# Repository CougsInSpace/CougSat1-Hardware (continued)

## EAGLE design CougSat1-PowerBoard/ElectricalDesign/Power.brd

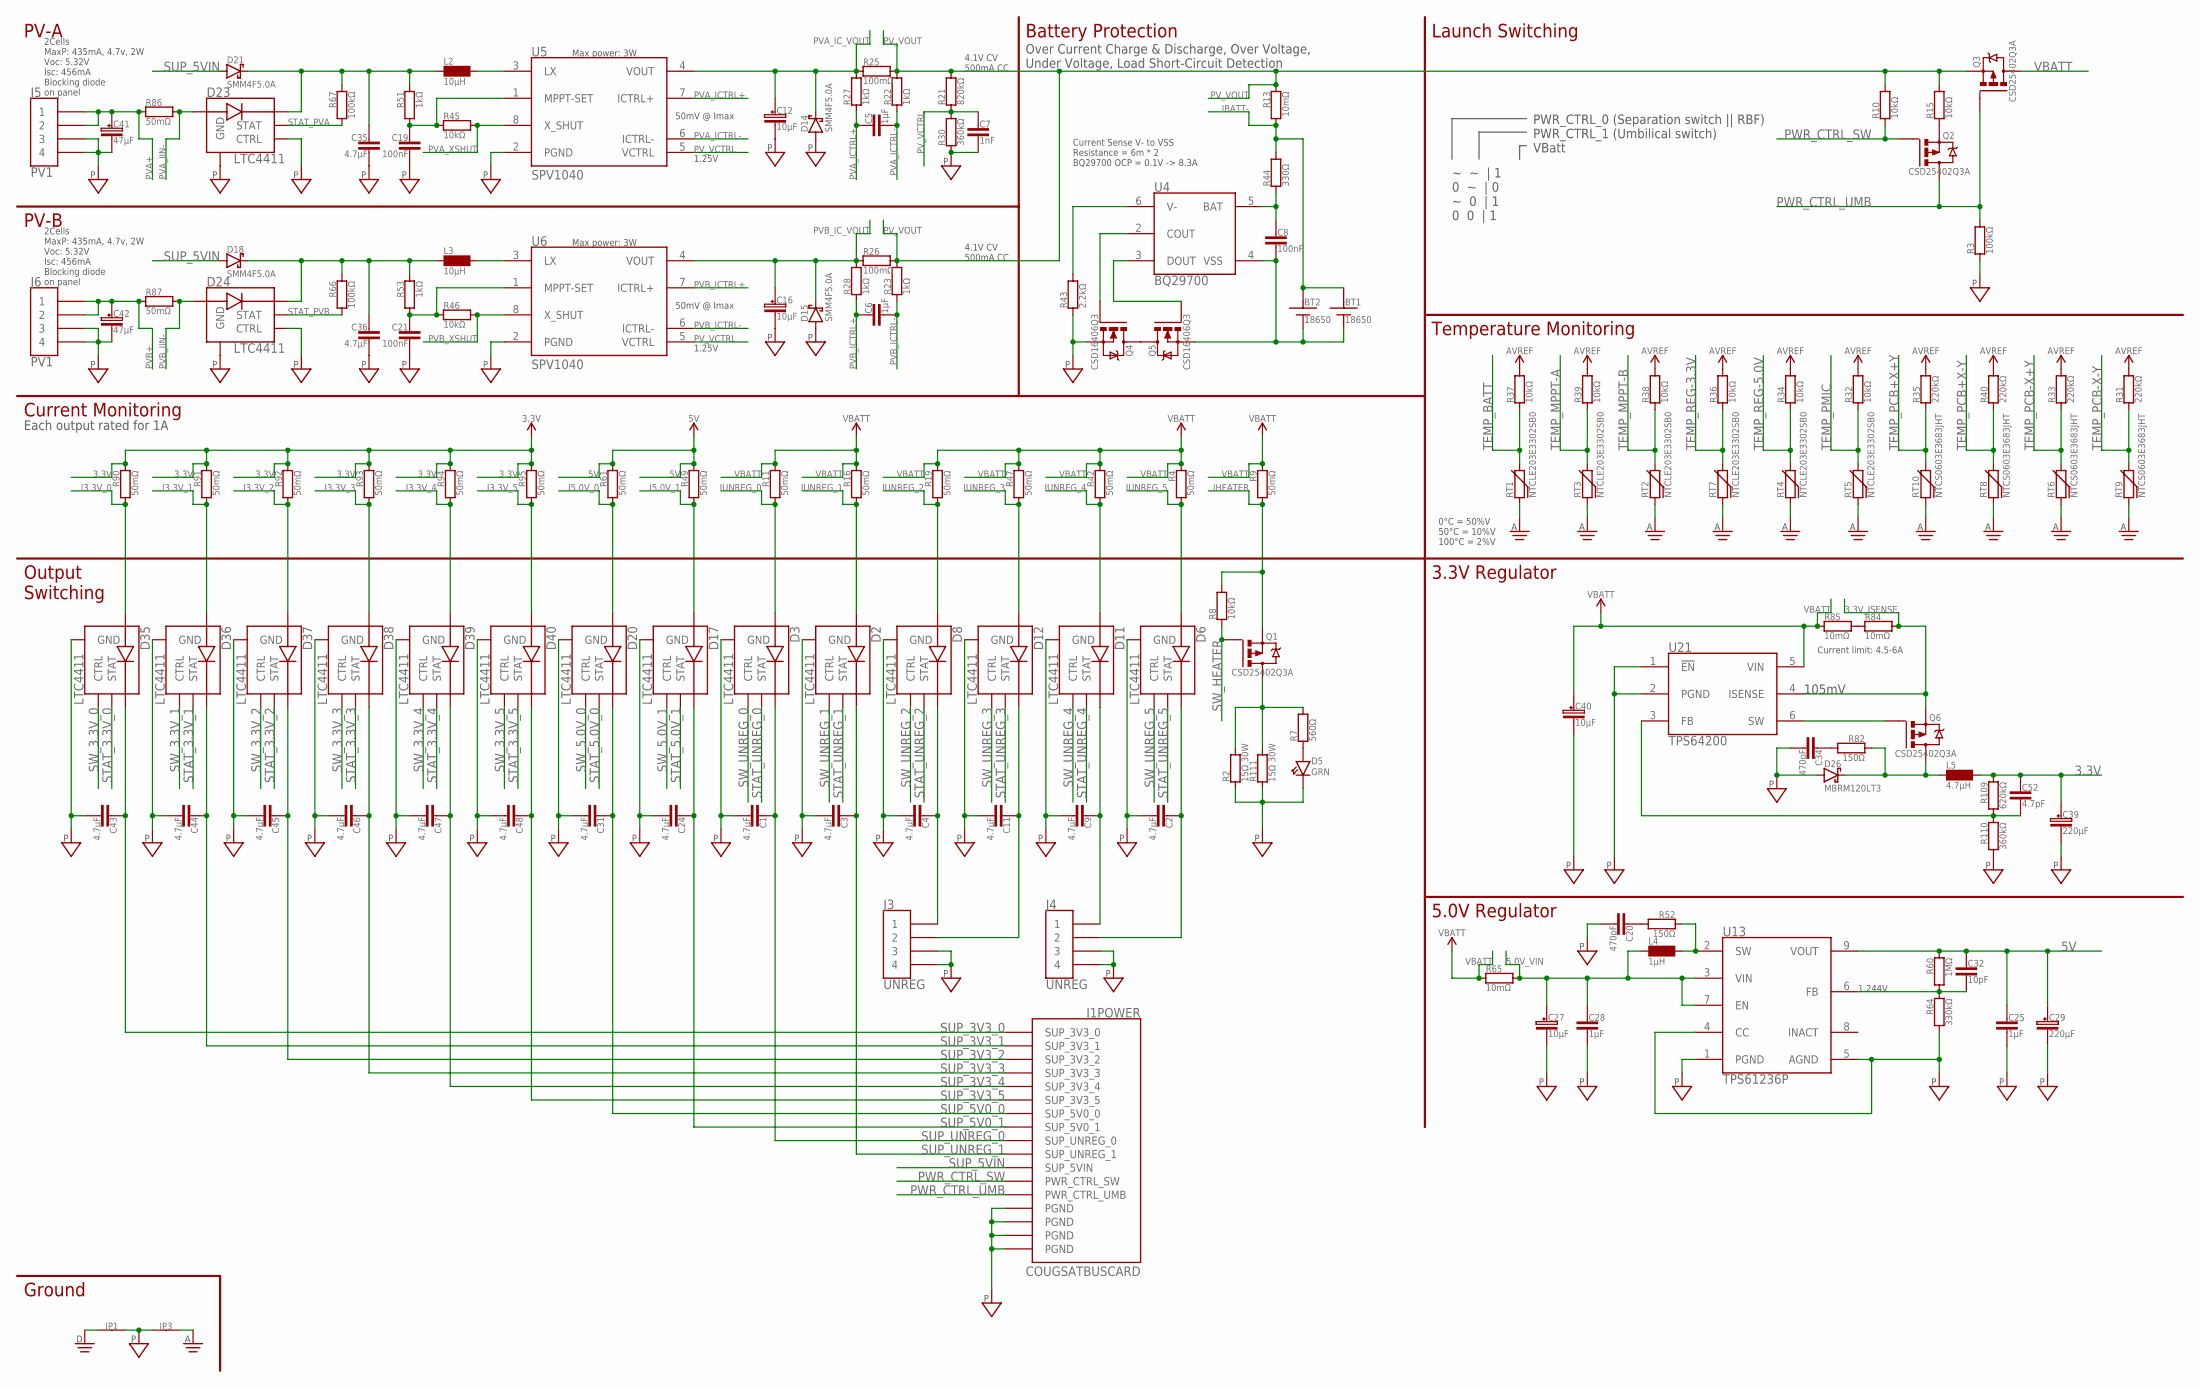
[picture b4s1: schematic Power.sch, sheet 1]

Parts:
BT1, BT2: 18650; BAT-18650SOLDER
C1, C2, C3, C4, C9, C11, C24, C31, C35, C36, C43, C44, C45, C46, C47, C48: 4.7µF; 3216
C5, C6, C25, C28: 1µF; 1608
C7: 1nF; 1608
C8, C19, C21: 100nF; 1608
C12, C16, C27, C40: 10µF; 4028-POL
C20, C34: 470pF; 1608
C29, C39: 220µF; 7132-POL
C32: 10pF; 1608
C41, C42: 47µF; 4028-POL
C52: 4.7pF; 1608
D2, D3, D6, D8, D11, D12, D17, D20, D23, D24, D35, D36, D37, D38, D39, D40: LTC4411; SOT23-5
D5: GRN; 1608-POL
D14, D15, D18, D21: SMM4F5.0A; STMITE
D26: MBRM120LT3; POWERMITE1
J1: COUGSATBUSCARD; COUGSATBUS_MALE-SODIMM
J3, J4: UNREG; 1X04_PICOLOCK1.5MM
J5, J6: PV1; 1X04_PICOLOCK1.5MM
JP1, JP3: SHORTCIRCUIT1608JUMPER; 1608
L2, L3: 10µH; INDUCTOR-LPS6235
L4: 1µH; INDUCTOR-XAL7030
L5: 4.7µH; INDUCTOR-XAL7030
Q1, Q2, Q3, Q6: CSD25402Q3A; SON-3.3X3.3MM
Q4, Q5: CSD16406Q3; SON-3.3X3.3MM
R2, R111: 15Ω 30W; TO220-2
R3, R66, R67: 100kΩ; 1608
R4, R9, R11, R16, R19, R42, R47, R49, R61, R86, R87, R90, R91, R92, R93, R94, R95: 50mΩ; 1608
R7: 560Ω; 1608
R8, R10, R15, R32, R34, R36, R37, R38, R39, R45, R46: 10kΩ; 1608
R13, R65, R84, R85: 10mΩ; 3216
R21: 820kΩ; 1608
R22, R23, R27, R28, R51, R53: 1kΩ; 1608
R25, R26: 100mΩ; 1608
R30, R110: 360kΩ; 1608
R31, R33, R35, R40: 220kΩ; 1608
R43: 2.2kΩ; 1608
R44: 330Ω; 1608
R52, R82: 150Ω; 1608
R60: 1MΩ; 1608
R64: 330kΩ; 1608
R109: 620kΩ; 1608
RT1, RT2, RT3, RT4, RT5, RT7: NTCLE203E3302SB0; 1X02_THERMISTOR
RT6, RT8, RT9, RT10: NTCS0603E3683JHT; 1608
U4: BQ29700; SON6-1.5X1.5MM
U5, U6: SPV1040; TSSOP8
U13: TPS61236P; QFN-TPS61236P
U21: TPS64200; SOT23-6

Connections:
3.3V: C39.A, C52.1, L5.2 (1), R90.1, R91.1, R92.1, R93.1, R94.1, R95.1, R109.1; also elsewhere on the board
3.3V_FB: C52.2, R109.2, R110.1, U21.3 (FB)
3.3V_ISENSE: Q6.5 (S), Q6.6 (S), Q6.7 (S), Q6.8 (S), Q6.PAD (S), R84.2, U21.4 (ISENSE); also elsewhere on the board
3.3V_LSW: D26.C, L5.11 (2), Q6.1 (D), Q6.2 (D), Q6.3 (D), R82.1
3.3V_RISENSE: R84.1, R85.2
3.3V_SNUBBER: C34.1, R82.2
3.3V_SW: Q6.4 (G), U21.6 (SW)
5.0V_FB: C32.2, R60.2, R64.1, U13.6 (FB)
5.0V_SNUBBER: C20.1, R52.2
5.0V_SW: L4.2 (1), R52.1, U13.2 (SW)
5.0V_VIN: C27.A, C28.1, L4.11 (2), R65.2, U13.3 (VIN), U13.7 (EN); also elsewhere on the board
5V: C25.1, C29.A, C32.1, R49.1, R60.1, R61.1, U13.9 (VOUT); also elsewhere on the board
AGND: JP3.2, RT1.1, RT2.1, RT3.1, RT4.1, RT5.1, RT6.1, RT7.1, RT8.1, RT9.1, RT10.1; also elsewhere on the board
AVREF: R31.2, R32.2, R33.2, R34.2, R35.2, R36.2, R37.2, R38.2, R39.2, R40.2; also elsewhere on the board
BATTPROTECTDOUT: Q5.4 (G), U4.3 (DOUT)
BATTPROTECT_BAT: C8.1, R44.1, U4.5 (BAT)
BATTPROTECT_COUT: Q4.4 (G), U4.2 (COUT)
BATTPROTECT_SW: Q4.5 (D), Q4.6 (D), Q4.7 (D), Q4.8 (D), Q4.PAD (D), Q5.5 (D), Q5.6 (D), Q5.7 (D), Q5.8 (D), Q5.PAD (D)
BATTPROTECT_V-: R43.2, U4.6 (V-)
BATTPROTECT_VSS: BT1.A, BT2.A, C8.2, Q5.1 (S), Q5.2 (S), Q5.3 (S), U4.4 (VSS)
DGND: JP1.1; also elsewhere on the board
I3.3V_0: D35.1 (IN), R90.2; also elsewhere on the board
I3.3V_1: D36.1 (IN), R91.2; also elsewhere on the board
I3.3V_2: D37.1 (IN), R92.2; also elsewhere on the board
I3.3V_3: D38.1 (IN), R93.2; also elsewhere on the board
I3.3V_4: D39.1 (IN), R94.2; also elsewhere on the board
I3.3V_5: D40.1 (IN), R95.2; also elsewhere on the board
I5.0V_0: D20.1 (IN), R61.2; also elsewhere on the board
I5.0V_1: D17.1 (IN), R49.2; also elsewhere on the board
IBATT-: BT1.C, BT2.C, R13.2, R44.2; also elsewhere on the board
IHEATER: Q1.5 (S), Q1.6 (S), Q1.7 (S), Q1.8 (S), Q1.PAD (S), R8.2, R9.2; also elsewhere on the board
IUNREG_0: D3.1 (IN), R11.2; also elsewhere on the board
IUNREG_1: D2.1 (IN), R16.2; also elsewhere on the board
IUNREG_2: D8.1 (IN), R19.2; also elsewhere on the board
IUNREG_3: D12.1 (IN), R47.2; also elsewhere on the board
IUNREG_4: D11.1 (IN), R42.2; also elsewhere on the board
IUNREG_5: D6.1 (IN), R4.2; also elsewhere on the board
MPPTA_VIN: C35.1, D21.A (C), D23.5 (OUT), L2.2, R51.1, R67.1
MPPTB_VIN: C36.1, D18.A (C), D24.5 (OUT), L3.2, R53.1, R66.1
PGND: C1.2, C2.2, C3.2, C4.2, C7.2, C9.2, C11.2, C12.C, C16.C, C19.2, C20.2, C21.2, C24.2, C25.2, C27.C, C28.2, C29.C, C31.2, C34.2, C35.2, C36.2, C39.C, C40.C, C41.C, C42.C, C43.2, C44.2, C45.2, C46.2, C47.2, C48.2, D2.2 (GND), D3.2 (GND), D5.C, D6.2 (GND), D8.2 (GND), D11.2 (GND), D12.2 (GND), D14.C (A), D15.C (A), D17.2 (GND), D20.2 (GND), D23.2 (GND), D23.3 (CTRL), D24.2 (GND), D24.3 (CTRL), D26.A, D35.2 (GND), D36.2 (GND), D37.2 (GND), D38.2 (GND), D39.2 (GND), D40.2 (GND), J1.1 (PGND), J1.3 (PGND), J1.5 (PGND), J1.7 (PGND), J1.9 (PGND), J1.11 (PGND), J1.13 (PGND), J1.15 (PGND), J1.17 (PGND), J1.19 (PGND), J1.41 (PGND), J1.43 (PGND), J1.45 (PGND), J1.47 (PGND), J1.49 (PGND), J1.51 (PGND), J1.53 (PGND), J1.55 (PGND), J1.57 (PGND), J1.59 (PGND), J1.61 (PGND), J1.63 (PGND), J1.65 (PGND), J1.67 (PGND), J1.69 (PGND), J1.82 (PGND), J1.84 (PGND), J1.86 (PGND), J1.88 (PGND), J1.90 (PGND), J1.92 (PGND), J1.94 (PGND), J1.96 (PGND), J1.98 (PGND), J1.100 (PGND), J1.102 (PGND), J1.104 (PGND), J1.106 (PGND), J1.108 (PGND), J1.110 (PGND), J1.112 (PGND), J1.114 (PGND), J1.116 (PGND), J1.118 (PGND), J1.120 (PGND), J1.122 (PGND), J1.124 (PGND), J1.126 (PGND), J1.128 (PGND), J1.130 (PGND), J1.131 (PGND), J1.132 (PGND), J1.133 (PGND), J1.134 (PGND), J1.135 (PGND), J1.136 (PGND), J1.137 (PGND), J1.138 (PGND), J1.139 (PGND), J1.140 (PGND), J3.3, J3.4, J4.3, J4.4, J5.3, J5.4, J6.3, J6.4, JP1.2, JP3.1, Q4.1 (S), Q4.2 (S), Q4.3 (S), R2.1, R3.1, R30.1, R43.1, R64.2, R110.2, R111.1, U5.2 (PGND), U6.2 (PGND), U13.1 (PGND), U13.4 (CC), U13.5 (AGND), U21.1 (!EN), U21.2 (PGND); also elsewhere on the board
PVA+: C41.A, J5.1, J5.2, R86.1; also elsewhere on the board
PVA_ICTRL+: C5.1, R27.1, U5.7 (ICTRL+)
PVA_ICTRL-: C5.2, R22.1, U5.6 (ICTRL-)
PVA_IC_VOUT: C12.A, D14.A (C), R25.1, R27.2, U5.4 (VOUT); also elsewhere on the board
PVA_IIN-: D23.1 (IN), R86.2; also elsewhere on the board
PVA_LX: L2.1, U5.3 (LX)
PVA_MPPTSET: C19.1, R45.1, R51.2, U5.1 (MPPT-SET)
PVA_XSHUT: R45.2, U5.8 (X_SHUT); also elsewhere on the board
PVB+: C42.A, J6.1, J6.2, R87.1; also elsewhere on the board
PVB_ICTRL+: C6.1, R28.1, U6.7 (ICTRL+)
PVB_ICTRL-: C6.2, R23.1, U6.6 (ICTRL-)
PVB_IC_VOUT: C16.A, D15.A (C), R26.1, R28.2, U6.4 (VOUT); also elsewhere on the board
PVB_IIN-: D24.1 (IN), R87.2; also elsewhere on the board
PVB_LX: L3.1, U6.3 (LX)
PVB_MPPTSET: C21.1, R46.1, R53.2, U6.1 (MPPT-SET)
PVB_XSHUT: R46.2, U6.8 (X_SHUT); also elsewhere on the board
PV_VCTRL: C7.1, R21.1, R30.2, U5.5 (VCTRL), U6.5 (VCTRL)
PV_VOUT: Q3.5 (S), Q3.6 (S), Q3.7 (S), Q3.8 (S), Q3.PAD (S), R10.2, R13.1, R15.2, R21.2, R22.2, R23.2, R25.2, R26.2; also elsewhere on the board
PWR_CTRL_0_SW+: Q2.5 (S), Q2.6 (S), Q2.7 (S), Q2.8 (S), Q2.PAD (S), R15.1
PWR_CTRL_SW: J1.166 (PWR_CTRL_SW), J1.168 (PWR_CTRL_SW), Q2.4 (G), R10.1
PWR_CTRL_UMB: J1.170 (PWR_CTRL_UMB), J1.172 (PWR_CTRL_UMB), Q2.1 (D), Q2.2 (D), Q2.3 (D), Q3.4 (G), R3.2
STAT_3.3V_0: D35.4 (STAT); also elsewhere on the board
STAT_3.3V_1: D36.4 (STAT); also elsewhere on the board
STAT_3.3V_2: D37.4 (STAT); also elsewhere on the board
STAT_3.3V_3: D38.4 (STAT); also elsewhere on the board
STAT_3.3V_4: D39.4 (STAT); also elsewhere on the board
STAT_3.3V_5: D40.4 (STAT); also elsewhere on the board
STAT_5.0V_0: D20.4 (STAT); also elsewhere on the board
STAT_5.0V_1: D17.4 (STAT); also elsewhere on the board
STAT_HEATER: D5.A, R7.1
STAT_PVA: D23.4 (STAT), R67.2; also elsewhere on the board
STAT_PVB: D24.4 (STAT), R66.2; also elsewhere on the board
STAT_UNREG_0: D3.4 (STAT); also elsewhere on the board
STAT_UNREG_1: D2.4 (STAT); also elsewhere on the board
STAT_UNREG_2: D8.4 (STAT); also elsewhere on the board
STAT_UNREG_3: D12.4 (STAT); also elsewhere on the board
STAT_UNREG_4: D11.4 (STAT); also elsewhere on the board
STAT_UNREG_5: D6.4 (STAT); also elsewhere on the board
SUP_3V3_0: C43.1, D35.5 (OUT), J1.2 (SUP_3V3_0), J1.4 (SUP_3V3_0), J1.6 (SUP_3V3_0), J1.8 (SUP_3V3_0), J1.10 (SUP_3V3_0)
SUP_3V3_1: C44.1, D36.5 (OUT), J1.12 (SUP_3V3_1), J1.14 (SUP_3V3_1), J1.16 (SUP_3V3_1), J1.18 (SUP_3V3_1), J1.20 (SUP_3V3_1)
SUP_3V3_2: C45.1, D37.5 (OUT), J1.21 (SUP_3V3_2), J1.23 (SUP_3V3_2), J1.25 (SUP_3V3_2), J1.27 (SUP_3V3_2), J1.29 (SUP_3V3_2), J1.31 (SUP_3V3_2), J1.33 (SUP_3V3_2), J1.35 (SUP_3V3_2), J1.37 (SUP_3V3_2), J1.39 (SUP_3V3_2)
SUP_3V3_3: C46.1, D38.5 (OUT), J1.22 (SUP_3V3_3), J1.24 (SUP_3V3_3), J1.26 (SUP_3V3_3), J1.28 (SUP_3V3_3), J1.30 (SUP_3V3_3), J1.32 (SUP_3V3_3), J1.34 (SUP_3V3_3), J1.36 (SUP_3V3_3), J1.38 (SUP_3V3_3), J1.40 (SUP_3V3_3)
SUP_3V3_4: C47.1, D39.5 (OUT), J1.42 (SUP_3V3_4), J1.44 (SUP_3V3_4), J1.46 (SUP_3V3_4), J1.48 (SUP_3V3_4), J1.50 (SUP_3V3_4)
SUP_3V3_5: C48.1, D40.5 (OUT), J1.52 (SUP_3V3_5), J1.54 (SUP_3V3_5), J1.56 (SUP_3V3_5), J1.58 (SUP_3V3_5), J1.60 (SUP_3V3_5)
SUP_5V0_0: C31.1, D20.5 (OUT), J1.62 (SUP_5V0_0), J1.64 (SUP_5V0_0), J1.66 (SUP_5V0_0), J1.68 (SUP_5V0_0), J1.70 (SUP_5V0_0), J1.72 (SUP_5V0_0), J1.74 (SUP_5V0_0), J1.76 (SUP_5V0_0), J1.78 (SUP_5V0_0), J1.80 (SUP_5V0_0)
SUP_5V0_1: C24.1, D17.5 (OUT), J1.71 (SUP_5V0_1), J1.73 (SUP_5V0_1), J1.75 (SUP_5V0_1), J1.77 (SUP_5V0_1), J1.79 (SUP_5V0_1), J1.81 (SUP_5V0_1), J1.83 (SUP_5V0_1), J1.85 (SUP_5V0_1), J1.87 (SUP_5V0_1), J1.89 (SUP_5V0_1)
SUP_5VIN: D18.C (A), D21.C (A), J1.182 (SUP_5VIN), J1.184 (SUP_5VIN), J1.186 (SUP_5VIN), J1.188 (SUP_5VIN), J1.190 (SUP_5VIN), J1.192 (SUP_5VIN), J1.194 (SUP_5VIN), J1.196 (SUP_5VIN), J1.198 (SUP_5VIN), J1.200 (SUP_5VIN)
SUP_HEATER: Q1.1 (D), Q1.2 (D), Q1.3 (D), R2.3 (2), R7.2, R111.3 (2)
SUP_UNREG_0: C1.1, D3.5 (OUT), J1.91 (SUP_UNREG_0), J1.93 (SUP_UNREG_0), J1.95 (SUP_UNREG_0), J1.97 (SUP_UNREG_0), J1.99 (SUP_UNREG_0), J1.101 (SUP_UNREG_0), J1.103 (SUP_UNREG_0), J1.105 (SUP_UNREG_0), J1.107 (SUP_UNREG_0), J1.109 (SUP_UNREG_0)
SUP_UNREG_1: C3.1, D2.5 (OUT), J1.111 (SUP_UNREG_1), J1.113 (SUP_UNREG_1), J1.115 (SUP_UNREG_1), J1.117 (SUP_UNREG_1), J1.119 (SUP_UNREG_1), J1.121 (SUP_UNREG_1), J1.123 (SUP_UNREG_1), J1.125 (SUP_UNREG_1), J1.127 (SUP_UNREG_1), J1.129 (SUP_UNREG_1)
SUP_UNREG_2: C4.1, D8.5 (OUT), J3.1
SUP_UNREG_3: C11.1, D12.5 (OUT), J3.2
SUP_UNREG_4: C9.1, D11.5 (OUT), J4.1
SUP_UNREG_5: C2.1, D6.5 (OUT), J4.2
SW_3.3V_0: D35.3 (CTRL); also elsewhere on the board
SW_3.3V_1: D36.3 (CTRL); also elsewhere on the board
SW_3.3V_2: D37.3 (CTRL); also elsewhere on the board
SW_3.3V_3: D38.3 (CTRL); also elsewhere on the board
SW_3.3V_4: D39.3 (CTRL); also elsewhere on the board
SW_3.3V_5: D40.3 (CTRL); also elsewhere on the board
SW_5.0V_0: D20.3 (CTRL); also elsewhere on the board
SW_5.0V_1: D17.3 (CTRL); also elsewhere on the board
SW_HEATER: Q1.4 (G), R8.1; also elsewhere on the board
SW_UNREG_0: D3.3 (CTRL); also elsewhere on the board
SW_UNREG_1: D2.3 (CTRL); also elsewhere on the board
SW_UNREG_2: D8.3 (CTRL); also elsewhere on the board
SW_UNREG_3: D12.3 (CTRL); also elsewhere on the board
SW_UNREG_4: D11.3 (CTRL); also elsewhere on the board
SW_UNREG_5: D6.3 (CTRL); also elsewhere on the board
TEMP_BATT: R37.1, RT1.2; also elsewhere on the board
TEMP_MPPT-A: R39.1, RT3.2; also elsewhere on the board
TEMP_MPPT-B: R38.1, RT2.2; also elsewhere on the board
TEMP_PCB+X+Y: R35.1, RT10.2; also elsewhere on the board
TEMP_PCB+X-Y: R40.1, RT8.2; also elsewhere on the board
TEMP_PCB-X+Y: R33.1, RT6.2; also elsewhere on the board
TEMP_PCB-X-Y: R31.1, RT9.2; also elsewhere on the board
TEMP_PMIC: R32.1, RT5.2; also elsewhere on the board
TEMP_REG-3.3V: R36.1, RT7.2; also elsewhere on the board
TEMP_REG-5.0V: R34.1, RT4.2; also elsewhere on the board
VBATT: C40.A, Q3.1 (D), Q3.2 (D), Q3.3 (D), R4.1, R9.1, R11.1, R16.1, R19.1, R42.1, R47.1, R65.1, R85.1, U21.5 (VIN); also elsewhere on the board

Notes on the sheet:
2Cells MaxP: 435mA, 4.7v, 2W Voc: 5.32V Isc: 456mA Blocking diode on panel
PV-A
Max power: 3W
50mV @ Imax
1.25V
PV-B
Current Monitoring
Ground
Each output rated for 1A
4.1V CV 500mA CC
Battery Protection
Current Sense V- to VSS Resistance = 6m * 2 BQ29700 OCP = 0.1V -> 8.3A
Over Current Charge & Discharge, Over Voltage, Under Voltage, Load Short-Circuit Detection
Launch Switching
~ ~ | 1 0 ~ | 0 ~ 0 | 1 0 0 | 1
PWR_CTRL_0 (Separation switch || RBF) PWR_CTRL_1 (Umbilical switch) VBatt
Output Switching
3.3V Regulator
5.0V Regulator
105mV
Current limit: 4.5-6A
1.244V
Temperature Monitoring
0°C = 50%V 50°C = 10%V 100°C = 2%V

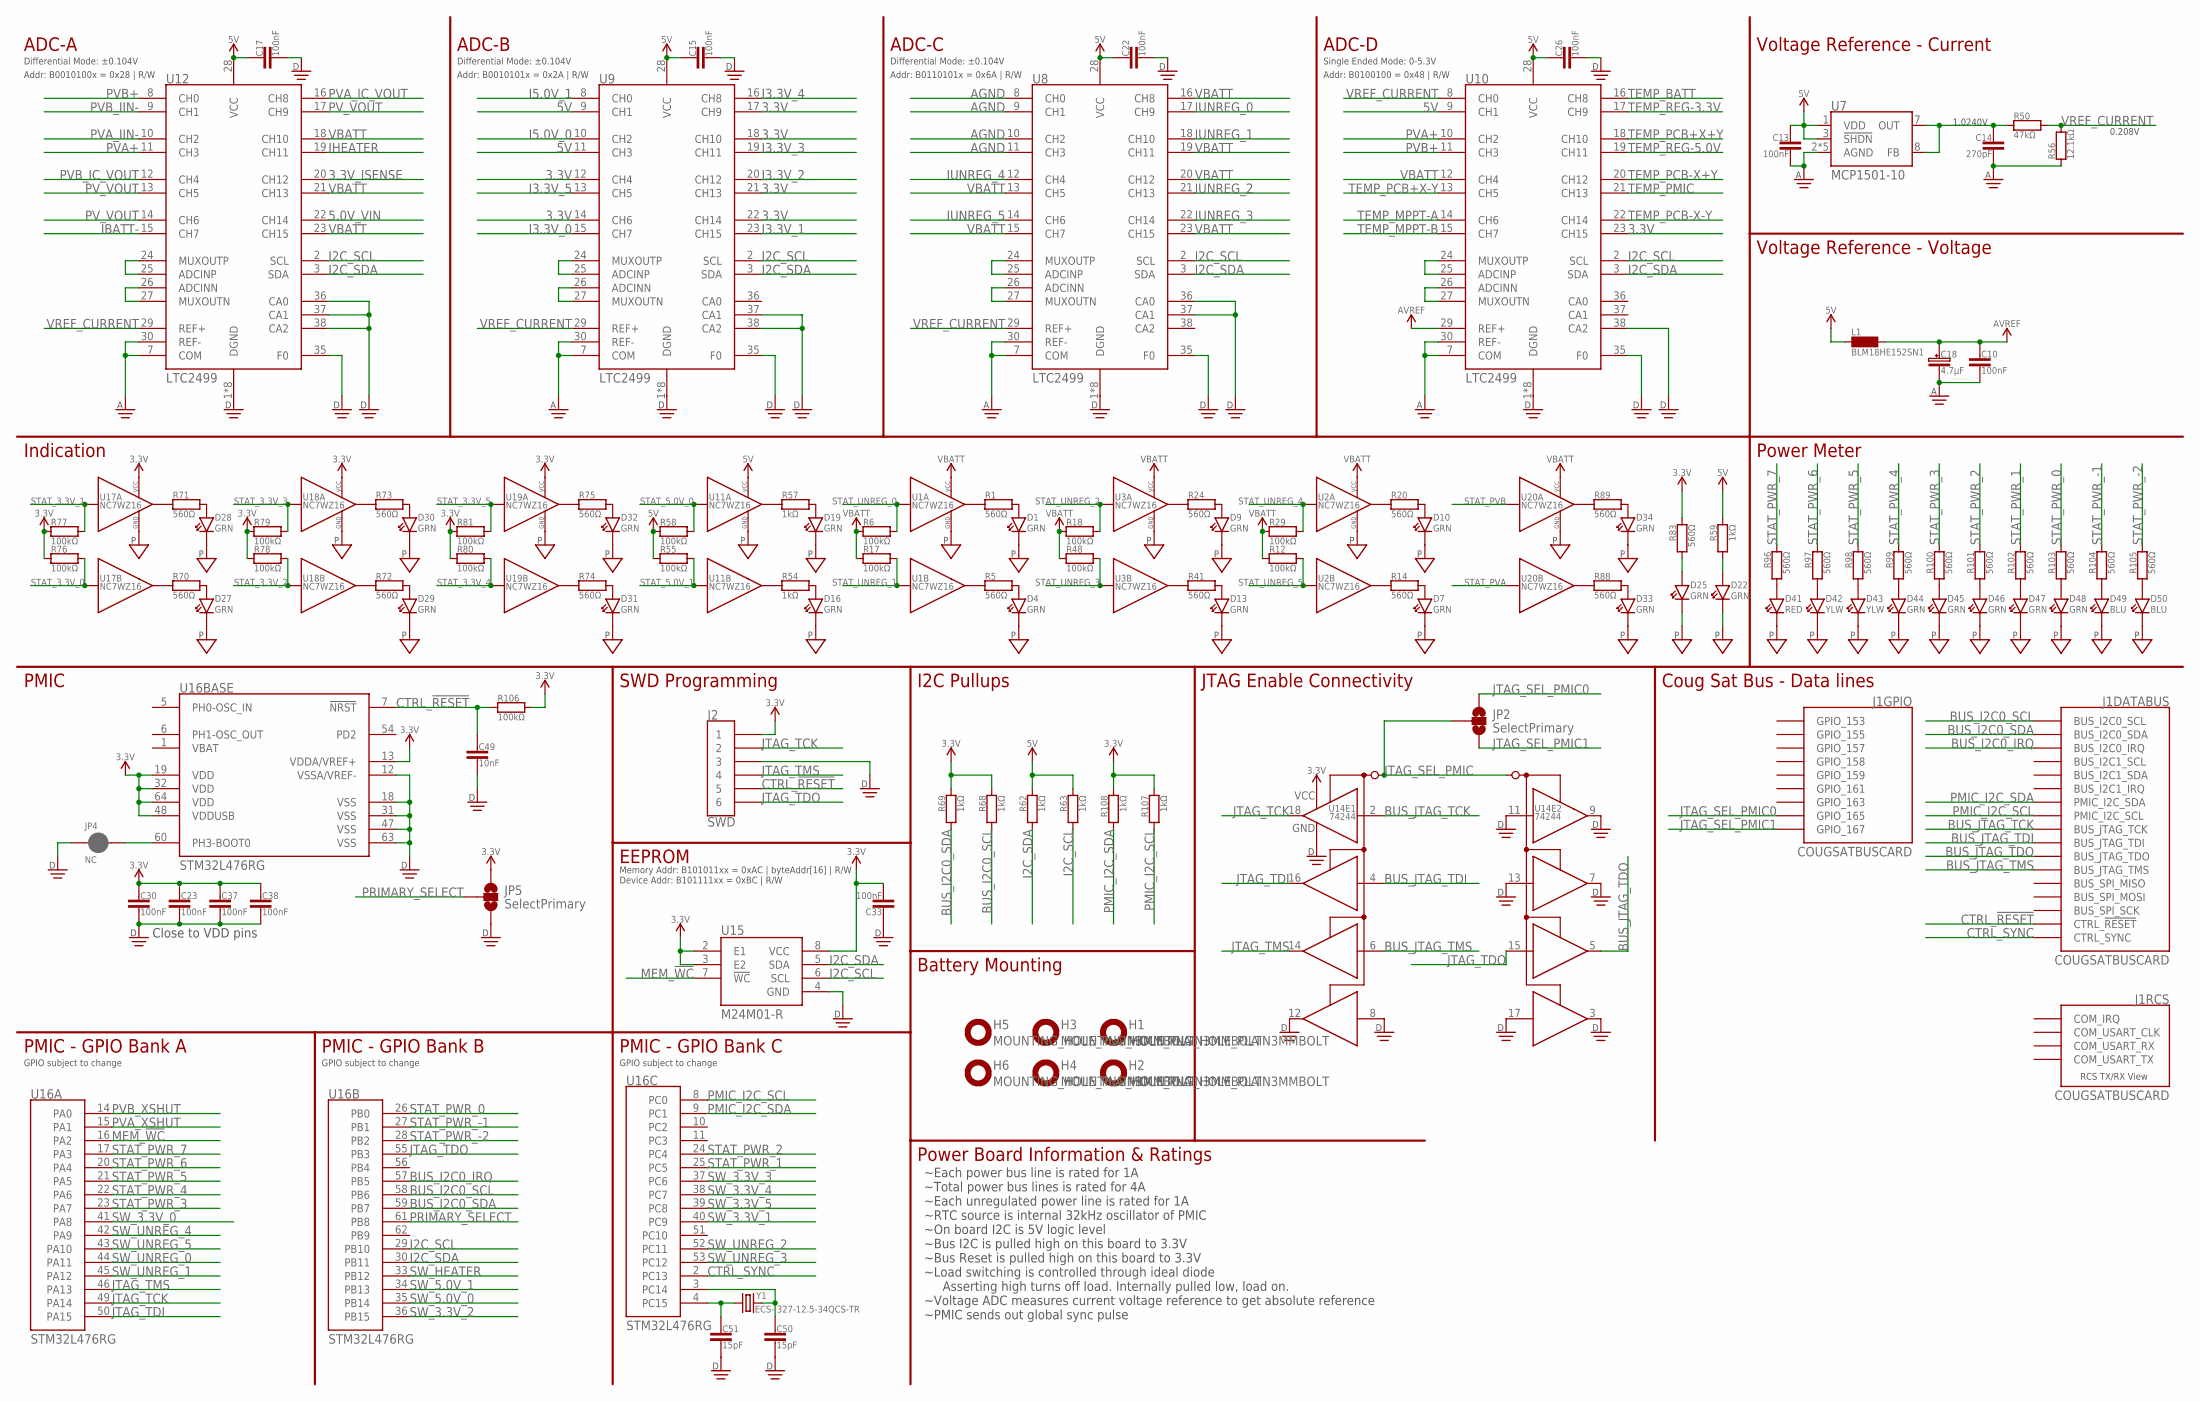
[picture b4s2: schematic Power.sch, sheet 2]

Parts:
C10, C13, C15, C17, C22, C23, C30, C33, C37, C38: 100nF; 1608
C14: 270pF; 1608
C18: 4.7µF; 4028-POL
C26: 100nF; 3216
C49: 10nF; 1608
C50, C51: 15pF; 1608
D1, D4, D7, D9, D10, D13, D16, D19, D22, D25, D27, D28, D29, D30, D31, D32, D33, D34, D44, D45, D46, D47, D48: GRN; 1608-POL
D41: RED; 1608-POL
D42, D43: YLW; 1608-POL
D49, D50: BLU; 1608-POL
H1, H2, H3, H4, H5, H6: MOUNTING_HOLE_PLAIN3MMBOLT; HOLE-3.3MM_PLAIN
J1: COUGSATBUSCARD; COUGSATBUS_MALE-SODIMM
J2: SWD; 1X06_SMD-2.54MM-R
JP2, JP5: SelectPrimary; SMT-JUMPER_3_NO_SILK
JP4: NC; SMT-JUMPER_2_NC_PASTE_SILK
L1: BLM18HE152SN1; 1608
R1, R5, R14, R20, R24, R41, R70, R71, R72, R73, R74, R75, R83, R88, R89, R96, R97, R98, R99, R100, R101, R102, R103, R104, R105: 560Ω; 1608
R6, R12, R17, R18, R29, R48, R55, R58, R76, R77, R78, R79, R80, R81, R106: 100kΩ; 1608
R50: 47kΩ; 1608
R54, R57, R59, R62, R63, R68, R69, R107, R108: 1kΩ; 1608
R56: 12.1kΩ; 1608
U1, U2, U3, U11, U17, U18, U19, U20: NC7WZ16; SC70
U7: MCP1501-10; WDFN8-2X2
U8, U9, U10, U12: LTC2499; QFN38-5X7
U14: 74244; QFN20-3.5X4.5
U15: M24M01-R; SO8
U16: STM32L476RG; QFP64-10X10
Y1: ECS-.327-12.5-34QCS-TR; CRYSTAL-3.2X1.5

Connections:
3.3V: C23.1, C30.1, C33.2, C37.1, C38.1, J2.1, JP5.1, R68.1, R69.1, R76.1, R77.1, R78.1, R79.1, R80.1, R81.1, R83.1, R106.2, R107.1, R108.1, U9.12 (CH4), U9.14 (CH6), U9.17 (CH9), U9.18 (CH10), U9.21 (CH13), U9.22 (CH14), U10.23 (CH15), U14.20 (VCC), U15.2 (E1), U15.3 (E2), U15.8 (VCC), U16.13 (VDDA/VREF+), U16.19 (VDD), U16.32 (VDD), U16.48 (VDDUSB), U16.64 (VDD), U17.5 (VCC), U18.5 (VCC), U19.5 (VCC); also elsewhere on the board
3.3V_ISENSE: U12.20 (CH12); also elsewhere on the board
5.0V_VIN: U12.22 (CH14); also elsewhere on the board
5V: C13.1, C15.1, C17.1, C22.1, C26.1, L1.2, R55.1, R58.1, R59.1, R62.1, R63.1, U7.1 (VDD), U7.3 (!SHDN), U8.28 (VCC), U9.9 (CH1), U9.11 (CH3), U9.28 (VCC), U10.9 (CH1), U10.28 (VCC), U11.5 (VCC), U12.28 (VCC); also elsewhere on the board
ADCA_ADCINN: U12.26 (ADCINN), U12.27 (MUXOUTN)
ADCA_ADCINP: U12.24 (MUXOUTP), U12.25 (ADCINP)
ADCB_ADCINN: U9.26 (ADCINN), U9.27 (MUXOUTN)
ADCB_ADCINP: U9.24 (MUXOUTP), U9.25 (ADCINP)
ADCC_ADCINN: U8.26 (ADCINN), U8.27 (MUXOUTN)
ADCC_ADCINP: U8.24 (MUXOUTP), U8.25 (ADCINP)
ADCF_ADCINN: U10.26 (ADCINN), U10.27 (MUXOUTN)
ADCF_ADCINP: U10.24 (MUXOUTP), U10.25 (ADCINP)
AGND: C10.2, C13.2, C14.2, C18.C, R56.1, U7.2 (AGND), U7.4 (AGND), U7.5 (AGND), U7.6 (AGND), U7.PAD (AGND), U8.7 (COM), U8.8 (CH0), U8.9 (CH1), U8.10 (CH2), U8.11 (CH3), U8.30 (REF-), U9.7 (COM), U9.30 (REF-), U10.7 (COM), U10.30 (REF-), U12.7 (COM), U12.30 (REF-); also elsewhere on the board
AVREF: C10.1, C18.A, L1.1, U10.29 (REF+); also elsewhere on the board
BUS_I2C0_IRQ: J1.177 (BUS_I2C0_IRQ), J1.179 (BUS_I2C0_IRQ), U16.57 (PB5)
BUS_I2C0_SCL: J1.173 (BUS_I2C0_SCL), J1.175 (BUS_I2C0_SCL), R68.2, U16.58 (PB6)
BUS_I2C0_SDA: J1.169 (BUS_I2C0_SDA), J1.171 (BUS_I2C0_SDA), R69.2, U16.59 (PB7)
BUS_JTAG_TCK: J1.185 (BUS_JTAG_TCK), J1.187 (BUS_JTAG_TCK), U14.2 (A1)
BUS_JTAG_TDI: J1.189 (BUS_JTAG_TDI), J1.191 (BUS_JTAG_TDI), U14.4 (A2)
BUS_JTAG_TDO: J1.193 (BUS_JTAG_TDO), J1.195 (BUS_JTAG_TDO), U14.5 (Y3)
BUS_JTAG_TMS: J1.197 (BUS_JTAG_TMS), J1.199 (BUS_JTAG_TMS), U14.6 (A3)
CTRL_!RESET: C49.1, J1.174 (CTRL_!RESET), J1.176 (CTRL_!RESET), J2.5, R106.1, U16.7 (!NRST)
CTRL_SYNC: J1.178 (CTRL_SYNC), J1.180 (CTRL_SYNC), U16.2 (PC13)
DGND: C15.2, C17.2, C22.2, C23.2, C26.2, C30.2, C33.1, C37.2, C38.2, C49.2, C50.2, C51.2, J2.3, JP4.1, JP5.3, U8.1 (DGND), U8.4 (DGND), U8.6 (DGND), U8.31 (DGND), U8.32 (DGND), U8.33 (DGND), U8.34 (DGND), U8.35 (F0), U8.36 (CA0), U8.37 (CA1), U8.PAD (DGND), U9.1 (DGND), U9.4 (DGND), U9.6 (DGND), U9.31 (DGND), U9.32 (DGND), U9.33 (DGND), U9.34 (DGND), U9.35 (F0), U9.37 (CA1), U9.38 (CA2), U9.PAD (DGND), U10.1 (DGND), U10.4 (DGND), U10.6 (DGND), U10.31 (DGND), U10.32 (DGND), U10.33 (DGND), U10.34 (DGND), U10.35 (F0), U10.38 (CA2), U10.PAD (DGND), U12.1 (DGND), U12.4 (DGND), U12.6 (DGND), U12.31 (DGND), U12.32 (DGND), U12.33 (DGND), U12.34 (DGND), U12.35 (F0), U12.36 (CA0), U12.37 (CA1), U12.38 (CA2), U12.PAD (DGND), U14.3 (Y4), U14.7 (Y2), U14.8 (A4), U14.9 (Y1), U14.10 (GND), U14.11 (A1), U14.12 (Y4), U14.13 (A2), U14.17 (A4), U14.PAD (GND), U15.4 (GND), U16.12 (VSSA/VREF-), U16.18 (VSS), U16.31 (VSS), U16.47 (VSS), U16.63 (VSS); also elsewhere on the board
I2C_SCL: R63.2, U8.2 (SCL), U9.2 (SCL), U10.2 (SCL), U12.2 (SCL), U15.6 (SCL), U16.29 (PB10)
I2C_SDA: R62.2, U8.3 (SDA), U9.3 (SDA), U10.3 (SDA), U12.3 (SDA), U15.5 (SDA), U16.30 (PB11)
I3.3V_0: U9.15 (CH7); also elsewhere on the board
I3.3V_1: U9.23 (CH15); also elsewhere on the board
I3.3V_2: U9.20 (CH12); also elsewhere on the board
I3.3V_3: U9.19 (CH11); also elsewhere on the board
I3.3V_4: U9.16 (CH8); also elsewhere on the board
I3.3V_5: U9.13 (CH5); also elsewhere on the board
I5.0V_0: U9.10 (CH2); also elsewhere on the board
I5.0V_1: U9.8 (CH0); also elsewhere on the board
IBATT-: U12.15 (CH7); also elsewhere on the board
IHEATER: U12.19 (CH11); also elsewhere on the board
IUNREG_0: U8.17 (CH9); also elsewhere on the board
IUNREG_1: U8.18 (CH10); also elsewhere on the board
IUNREG_2: U8.21 (CH13); also elsewhere on the board
IUNREG_3: U8.22 (CH14); also elsewhere on the board
IUNREG_4: U8.12 (CH4); also elsewhere on the board
IUNREG_5: U8.14 (CH6); also elsewhere on the board
JTAG_SEL_PMIC: JP2.2, U14.1 (!EN), U14.19 (!EN)
JTAG_SEL_PMIC0: J1.165 (GPIO_165), JP2.1
JTAG_SEL_PMIC1: J1.167 (GPIO_167), JP2.3
JTAG_TCK: J2.2, U14.18 (Y1), U16.49 (PA14)
JTAG_TDI: U14.16 (Y2), U16.50 (PA15)
JTAG_TDO: J2.6, U14.15 (A3), U16.55 (PB3)
JTAG_TMS: J2.4, U14.14 (Y3), U16.46 (PA13)
MEM_!WC: U15.7 (!WC), U16.16 (PA2)
OSC32_IN: C50.1, U16.3 (PC14), Y1.2
OSC32_OUT: C51.1, U16.4 (PC15), Y1.1
PGND: D1.C, D4.C, D7.C, D9.C, D10.C, D13.C, D16.C, D19.C, D22.C, D25.C, D27.C, D28.C, D29.C, D30.C, D31.C, D32.C, D33.C, D34.C, D41.C, D42.C, D43.C, D44.C, D45.C, D46.C, D47.C, D48.C, D49.C, D50.C, U1.2 (GND), U2.2 (GND), U3.2 (GND), U11.2 (GND), U17.2 (GND), U18.2 (GND), U19.2 (GND), U20.2 (GND); also elsewhere on the board
PMIC_BOOT0: JP4.2, U16.60 (PH3-BOOT0)
PMIC_I2C_SCL: J1.183 (PMIC_I2C_SCL), R107.2, U16.8 (PC0)
PMIC_I2C_SDA: J1.181 (PMIC_I2C_SDA), R108.2, U16.9 (PC1)
PRIMARY_SELECT: JP5.2, U16.61 (PB8)
PVA+: U10.10 (CH2), U12.11 (CH3); also elsewhere on the board
PVA_IC_VOUT: U12.16 (CH8); also elsewhere on the board
PVA_IIN-: U12.10 (CH2); also elsewhere on the board
PVA_XSHUT: U16.15 (PA1); also elsewhere on the board
PVB+: U10.11 (CH3), U12.8 (CH0); also elsewhere on the board
PVB_IC_VOUT: U12.12 (CH4); also elsewhere on the board
PVB_IIN-: U12.9 (CH1); also elsewhere on the board
PVB_XSHUT: U16.14 (PA0); also elsewhere on the board
PV_VOUT: U12.13 (CH5), U12.14 (CH6), U12.17 (CH9); also elsewhere on the board
STAT_3.3VON_LED: D25.A, R83.2
STAT_3.3V_0: R76.2, U17.3 (A); also elsewhere on the board
STAT_3.3V_0_BUFF: R70.1, U17.4 (Y)
STAT_3.3V_0_LED: D27.A, R70.2
STAT_3.3V_1: R77.2, U17.1 (A); also elsewhere on the board
STAT_3.3V_1_BUFF: R71.1, U17.6 (Y)
STAT_3.3V_1_LED: D28.A, R71.2
STAT_3.3V_2: R78.2, U18.3 (A); also elsewhere on the board
STAT_3.3V_2_BUFF: R72.1, U18.4 (Y)
STAT_3.3V_2_LED: D29.A, R72.2
STAT_3.3V_3: R79.2, U18.1 (A); also elsewhere on the board
STAT_3.3V_3_BUFF: R73.1, U18.6 (Y)
STAT_3.3V_3_LED: D30.A, R73.2
STAT_3.3V_4: R80.2, U19.3 (A); also elsewhere on the board
STAT_3.3V_4_BUFF: R74.1, U19.4 (Y)
STAT_3.3V_4_LED: D31.A, R74.2
STAT_3.3V_5: R81.2, U19.1 (A); also elsewhere on the board
STAT_3.3V_5_BUFF: R75.1, U19.6 (Y)
STAT_3.3V_5_LED: D32.A, R75.2
STAT_5.0VON_LED: D22.A, R59.2
STAT_5.0V_0: R58.2, U11.1 (A); also elsewhere on the board
STAT_5.0V_0_BUFF: R57.1, U11.6 (Y)
STAT_5.0V_0_LED: D19.A, R57.2
STAT_5.0V_1: R55.2, U11.3 (A); also elsewhere on the board
STAT_5.0V_1_BUFF: R54.1, U11.4 (Y)
STAT_5.0V_1_LED: D16.A, R54.2
STAT_PVA: U20.3 (A); also elsewhere on the board
STAT_PVA_BUFF: R88.1, U20.4 (Y)
STAT_PVA_LED: D33.A, R88.2
STAT_PVB: U20.1 (A); also elsewhere on the board
STAT_PVB_BUFF: R89.1, U20.6 (Y)
STAT_PVB_LED: D34.A, R89.2
STAT_PWR_0: R103.1, U16.26 (PB0)
STAT_PWR_0_LED: D48.A, R103.2
STAT_PWR_1: R102.1, U16.25 (PC5)
STAT_PWR_1_LED: D47.A, R102.2
STAT_PWR_2: R101.1, U16.24 (PC4)
STAT_PWR_2_LED: D46.A, R101.2
STAT_PWR_3: R100.1, U16.23 (PA7)
STAT_PWR_3_LED: D45.A, R100.2
STAT_PWR_4: R99.1, U16.22 (PA6)
STAT_PWR_4_LED: D44.A, R99.2
STAT_PWR_5: R98.1, U16.21 (PA5)
STAT_PWR_5_LED: D43.A, R98.2
STAT_PWR_6: R97.1, U16.20 (PA4)
STAT_PWR_6_LED: D42.A, R97.2
STAT_PWR_7: R96.1, U16.17 (PA3)
STAT_PWR_7_LED: D41.A, R96.2
STAT_PWR_-1: R104.1, U16.27 (PB1)
STAT_PWR_-1_LED: D49.A, R104.2
STAT_PWR_-2: R105.1, U16.28 (PB2)
STAT_PWR_-2_LED: D50.A, R105.2
STAT_UNREG_0: R6.2, U1.1 (A); also elsewhere on the board
STAT_UNREG_0_BUFF: R1.1, U1.6 (Y)
STAT_UNREG_0_LED: D1.A, R1.2
STAT_UNREG_1: R17.2, U1.3 (A); also elsewhere on the board
STAT_UNREG_1_BUFF: R5.1, U1.4 (Y)
STAT_UNREG_1_LED: D4.A, R5.2
STAT_UNREG_2: R18.2, U3.1 (A); also elsewhere on the board
STAT_UNREG_2_BUFF: R24.1, U3.6 (Y)
STAT_UNREG_2_LED: D9.A, R24.2
STAT_UNREG_3: R48.2, U3.3 (A); also elsewhere on the board
STAT_UNREG_3_BUFF: R41.1, U3.4 (Y)
STAT_UNREG_3_LED: D13.A, R41.2
STAT_UNREG_4: R29.2, U2.1 (A); also elsewhere on the board
STAT_UNREG_4_BUFF: R20.1, U2.6 (Y)
STAT_UNREG_4_LED: D10.A, R20.2
STAT_UNREG_5: R12.2, U2.3 (A); also elsewhere on the board
STAT_UNREG_5_BUFF: R14.1, U2.4 (Y)
STAT_UNREG_5_LED: D7.A, R14.2
SW_3.3V_0: U16.41 (PA8); also elsewhere on the board
SW_3.3V_1: U16.40 (PC9); also elsewhere on the board
SW_3.3V_2: U16.36 (PB15); also elsewhere on the board
SW_3.3V_3: U16.37 (PC6); also elsewhere on the board
SW_3.3V_4: U16.38 (PC7); also elsewhere on the board
SW_3.3V_5: U16.39 (PC8); also elsewhere on the board
SW_5.0V_0: U16.35 (PB14); also elsewhere on the board
SW_5.0V_1: U16.34 (PB13); also elsewhere on the board
SW_HEATER: U16.33 (PB12); also elsewhere on the board
SW_UNREG_0: U16.44 (PA11); also elsewhere on the board
SW_UNREG_1: U16.45 (PA12); also elsewhere on the board
SW_UNREG_2: U16.52 (PC11); also elsewhere on the board
SW_UNREG_3: U16.53 (PC12); also elsewhere on the board
SW_UNREG_4: U16.42 (PA9); also elsewhere on the board
SW_UNREG_5: U16.43 (PA10); also elsewhere on the board
TEMP_BATT: U10.16 (CH8); also elsewhere on the board
TEMP_MPPT-A: U10.14 (CH6); also elsewhere on the board
TEMP_MPPT-B: U10.15 (CH7); also elsewhere on the board
TEMP_PCB+X+Y: U10.18 (CH10); also elsewhere on the board
TEMP_PCB+X-Y: U10.13 (CH5); also elsewhere on the board
TEMP_PCB-X+Y: U10.20 (CH12); also elsewhere on the board
TEMP_PCB-X-Y: U10.22 (CH14); also elsewhere on the board
TEMP_PMIC: U10.21 (CH13); also elsewhere on the board
TEMP_REG-3.3V: U10.17 (CH9); also elsewhere on the board
TEMP_REG-5.0V: U10.19 (CH11); also elsewhere on the board
VBAT: U16.1 (VBAT)
VBATT: R6.1, R12.1, R17.1, R18.1, R29.1, R48.1, U1.5 (VCC), U2.5 (VCC), U3.5 (VCC), U8.13 (CH5), U8.15 (CH7), U8.16 (CH8), U8.19 (CH11), U8.20 (CH12), U8.23 (CH15), U10.12 (CH4), U12.18 (CH10), U12.21 (CH13), U12.23 (CH15), U20.5 (VCC); also elsewhere on the board
VREF_CURRENT: R50.2, R56.2, U8.29 (REF+), U9.29 (REF+), U10.8 (CH0), U12.29 (REF+)
VREF_CURRENT_OUT: C14.1, R50.1, U7.7 (OUT), U7.8 (FB)

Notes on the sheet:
Addr: B0010100x = 0x28 | R/W
Differential Mode: ±0.104V
ADC-A
Addr: B0010101x = 0x2A | R/W
ADC-B
Addr: B0110101x = 0x6A | R/W
ADC-C
Addr: B0100100 = 0x48 | R/W
Single Ended Mode: 0-5.3V
ADC-D
Voltage Reference - Current
1.0240V
0.208V
Voltage Reference - Voltage
PMIC
Coug Sat Bus - Data lines
~Each power bus line is rated for 1A ~Total power bus lines is rated for 4A ~Each unregulated power line is rated for 1A ~RTC source is internal 32kHz oscillator of PMIC ~On board I2C is 5V logic level ~Bus I2C is pulled high on this board to 3.3V ~Bus Reset is pulled high on this board to 3.3V ~Lo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
Power Board Information & Ratings
JTAG Enable Connectivity
Indication
Power Meter
I2C Pullups
PMIC - GPIO Bank A
PMIC - GPIO Bank B
PMIC - GPIO Bank C
GPIO subject to change
Close to VDD pins
Battery Mounting
SWD Programming
EEPROM
Memory Addr: B101011xx = 0xAC | byteAddr[16] | R/W Device Addr: B101111xx = 0xBC | R/W

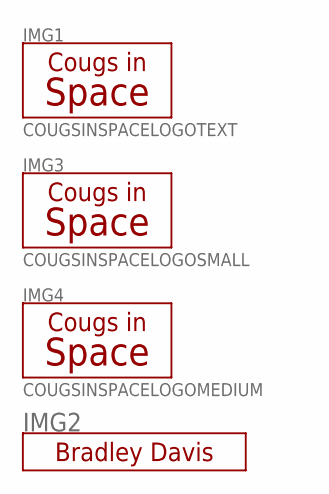
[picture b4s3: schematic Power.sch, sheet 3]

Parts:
IMG1: COUGSINSPACELOGOTEXT; COUGSINSPACETEXT
IMG2: Bradley Davis; SIGNATURE-BRADLEY
IMG3: COUGSINSPACELOGOSMALL; COUGSINSPACELOGO_SMALL
IMG4: COUGSINSPACELOGOMEDIUM; COUGSINSPACELOGO_MEDIUM
